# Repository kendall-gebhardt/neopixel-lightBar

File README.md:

# neopixel-lightBar
 A simple way to command Neopixels

This program allows the user to control brightness and temperature of a string of neopixels using a set of pushbuttons.
This is built around the Adafruit Metro Mini development board.

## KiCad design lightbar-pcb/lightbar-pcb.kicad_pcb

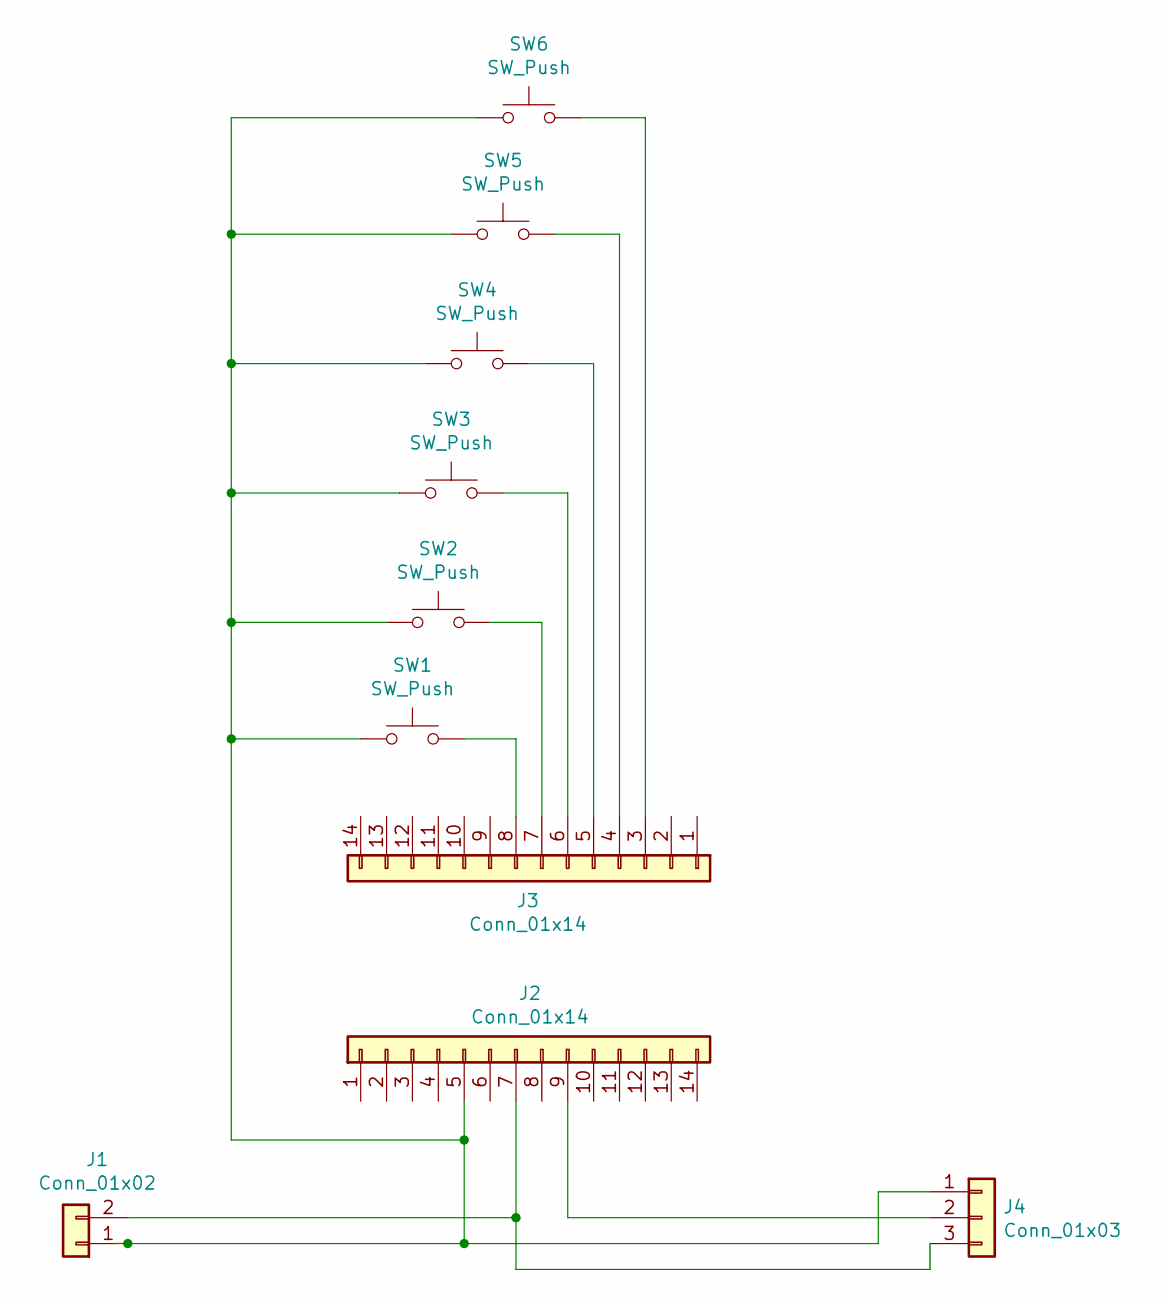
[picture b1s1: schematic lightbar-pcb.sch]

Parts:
J1: Conn_01x02; Molex_Micro-Fit_3.0_43650-0200_1x02_P3.00mm_Horizontal-with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
J2, J3: Conn_01x14; PinSocket_1x14_P2.54mm_Vertical
J4: Conn_01x03; Molex_Micro-Fit_3.0_43650-0300_1x03_P3.00mm_Horizontal-with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
SW1, SW2, SW3, SW4, SW5, SW6: SW_Push; SW_PUSH_6mm_H5mm-2pin-with3D

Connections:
unnamed: J1.1, J2.5, J4.1, SW1.1, SW2.1, SW3.1, SW4.1, SW5.1, SW6.1
unnamed: J1.2, J2.7, J4.3
unnamed: J2.9, J4.2
unnamed: J3.3, SW6.2
unnamed: J3.4, SW5.2
unnamed: J3.5, SW4.2
unnamed: J3.6, SW3.2
unnamed: J3.7, SW2.2
unnamed: J3.8, SW1.2

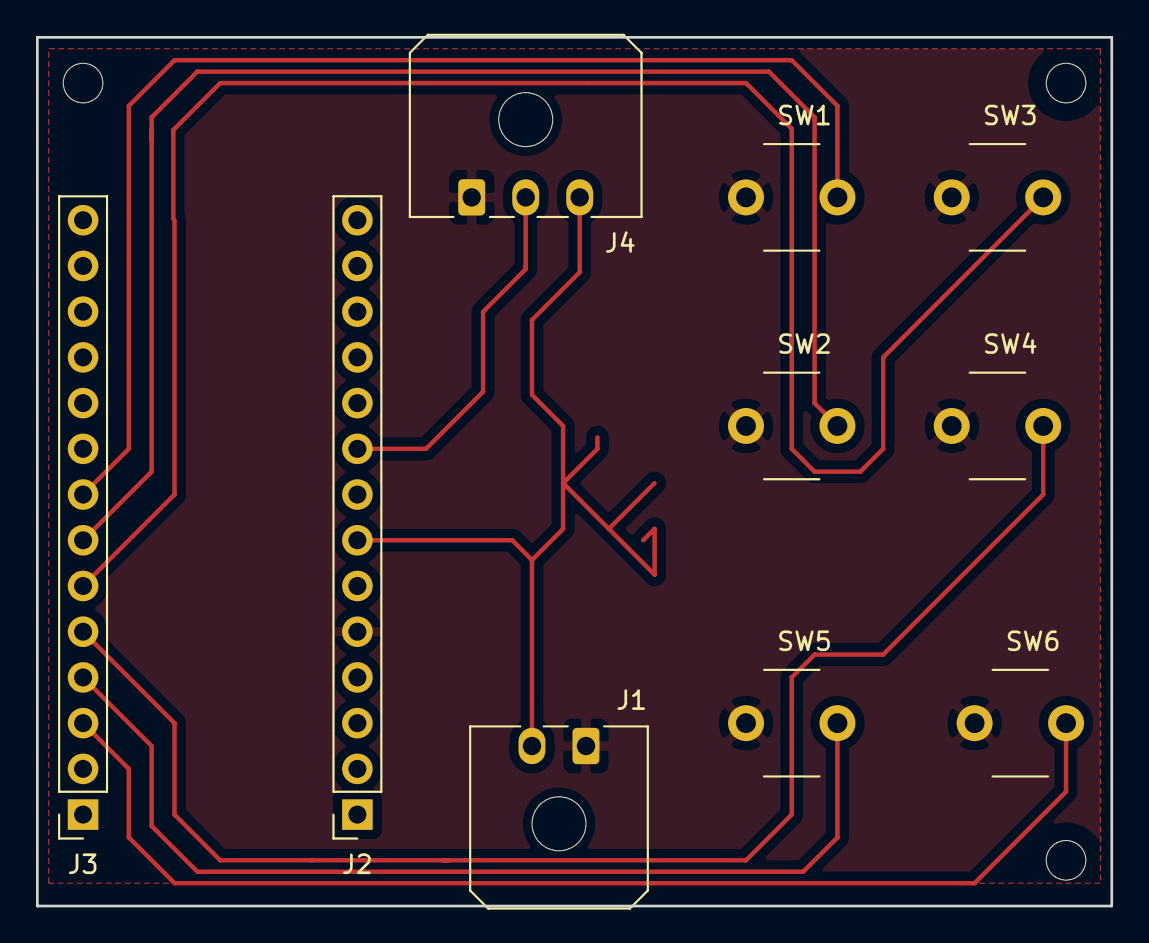
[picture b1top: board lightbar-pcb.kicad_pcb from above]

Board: 2 copper layers, 59.7 x 48.3 mm, 10 parts (0 on the bottom side), 9 nets.

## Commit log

2021-03-06 Arduino Code
    Arduino code to control a strip of 118 neopixels from pin A0. Brightness, temperature, and rainbow functions respond to button presses
2021-03-07 Add schematic and gerbers
    Schematic for the PCB as well as associated Gerber files
